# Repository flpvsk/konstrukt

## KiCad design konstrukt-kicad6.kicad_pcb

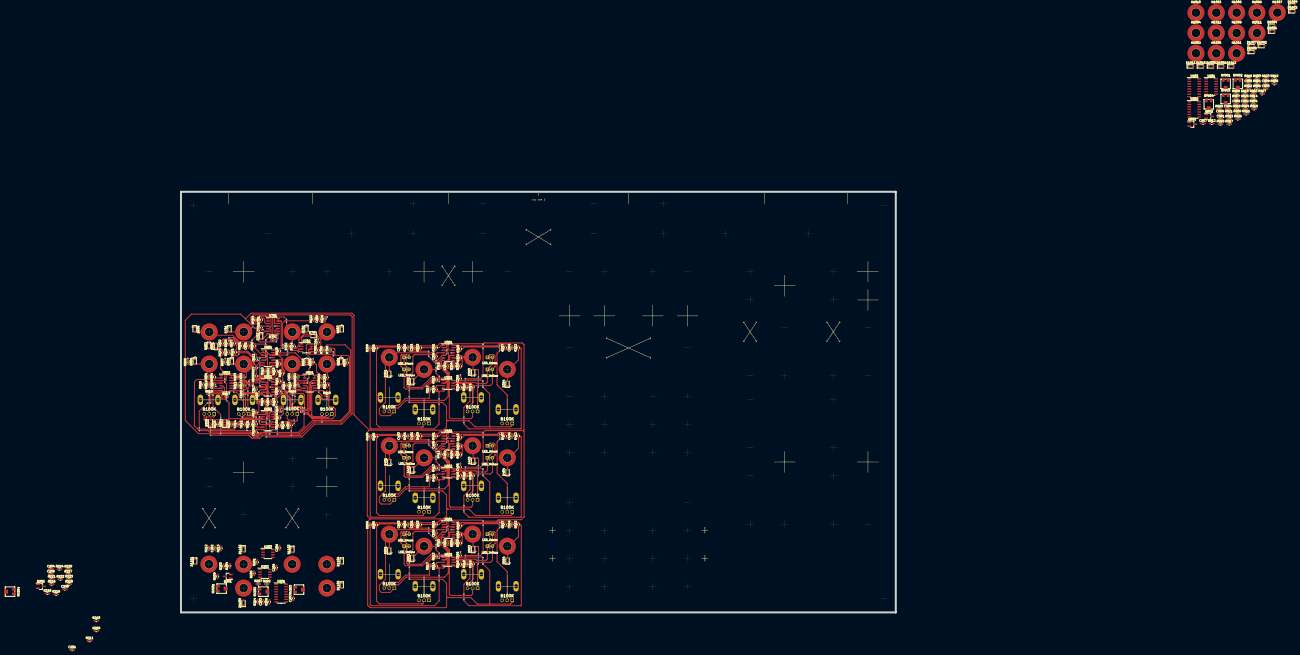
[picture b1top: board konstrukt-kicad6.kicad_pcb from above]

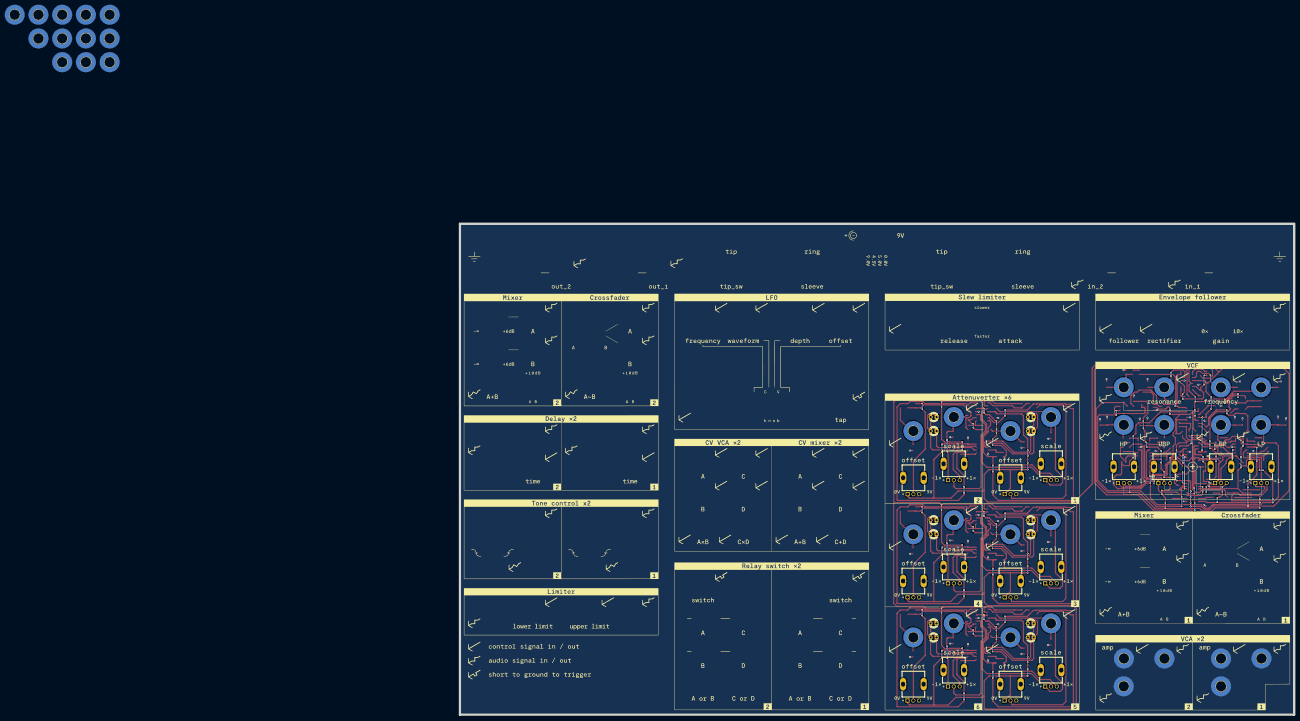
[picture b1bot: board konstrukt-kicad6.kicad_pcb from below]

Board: 2 copper layers, 356.9 x 210.0 mm, 361 parts (54 on the bottom side), 212 nets.

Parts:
C201, C205, C901, C903: 100p; C_0603_1608Metric_Pad1.08x0.95mm_HandSolder
C202, C203, C204, C206, C207, C208, C209, C305, C306, C405, C406, C505, C506, C601, C606, C612, C613, C615, C616, C701, C702, C801, C802, C803, C804, C805, C806, C907, C908, C909: 100n; C_0603_1608Metric_Pad1.08x0.95mm_HandSolder
C301, C302, C303, C304, C401, C402, C403, C404, C501, C502, C503, C504, C902, C904, C905, C906: 10p; C_0603_1608Metric_Pad1.08x0.95mm_HandSolder
C602, C605, C608, C614: 220p; C_0603_1608Metric_Pad1.08x0.95mm_HandSolder
C603, C604, C607, C610: 1.2n; C_0603_1608Metric_Pad1.08x0.95mm_HandSolder
D301, D302, D303, D304, D401, D402, D403, D404, D501, D502, D503, D504, D603, D606, D701, D702, D801, D802, D803, D804, D1001, D1002, D1003, D1004, D1005, D1006, D1007, D1008, D1009, D1010, D1011, D1012, D1101, D1102, D1103, D1104, D1105, D1106: D_TVS; D_SOD-323_HandSoldering
D305, D306, D405, D406, D505, D506: LED_Green; LED_D3.0mm
D307, D308, D407, D408, D507, D508: LED_Yellow; LED_D3.0mm
D601, D602, D703, D704: D; D_SOD-323_HandSoldering
D604, D605: D_Zener; D_SOD-123
H301: 2xAttenuverters1_1_In; MountingHole_4.3mm_M4_Pad_TopBottom
H302: 2xAttenuverters1_1_Out; MountingHole_4.3mm_M4_Pad_TopBottom
H303: 2xAttenuverters1_2_In; MountingHole_4.3mm_M4_Pad_TopBottom
H304: 2xAttenuverters1_2_Out; MountingHole_4.3mm_M4_Pad_TopBottom
H401: 2xAttenuverters2_1_In; MountingHole_4.3mm_M4_Pad_TopBottom
H402: 2xAttenuverters2_1_Out; MountingHole_4.3mm_M4_Pad_TopBottom
H403: 2xAttenuverters2_2_In; MountingHole_4.3mm_M4_Pad_TopBottom
H404: 2xAttenuverters2_2_Out; MountingHole_4.3mm_M4_Pad_TopBottom
H501: 2xAttenuverters3_1_In; MountingHole_4.3mm_M4_Pad_TopBottom
H502: 2xAttenuverters3_1_Out; MountingHole_4.3mm_M4_Pad_TopBottom
H503: 2xAttenuverters3_2_In; MountingHole_4.3mm_M4_Pad_TopBottom
H504: 2xAttenuverters3_2_Out; MountingHole_4.3mm_M4_Pad_TopBottom
H601: Main_Out; MountingHole_4.3mm_M4_Pad_TopBottom
H602: In; MountingHole_4.3mm_M4_Pad_TopBottom
H701: Freq_In; MountingHole_4.3mm_M4_Pad_TopBottom
H702: Res_In; MountingHole_4.3mm_M4_Pad_TopBottom
H801: HP_Out; MountingHole_4.3mm_M4_Pad_TopBottom
H802: UBP_Out; MountingHole_4.3mm_M4_Pad_TopBottom
H803: LBP_Out; MountingHole_4.3mm_M4_Pad_TopBottom
H804: LP_Out; MountingHole_4.3mm_M4_Pad_TopBottom
H1001, H1101: VCA1_In; MountingHole_4.3mm_M4_Pad_TopBottom
H1002, H1102: VCA1_CV_In; MountingHole_4.3mm_M4_Pad_TopBottom
H1003, H1103: VCA2_In; MountingHole_4.3mm_M4_Pad_TopBottom
H1004, H1104: VCA2_CV_In; MountingHole_4.3mm_M4_Pad_TopBottom
H1005, H1105: VCA1_Out; MountingHole_4.3mm_M4_Pad_TopBottom
H1006, H1106: VCA2_Out; MountingHole_4.3mm_M4_Pad_TopBottom
H1007: Mixer1_In1; MountingHole_4.3mm_M4_Pad_TopBottom
H1008: Mixer1_In2; MountingHole_4.3mm_M4_Pad_TopBottom
H1009: Mixer2_In1; MountingHole_4.3mm_M4_Pad_TopBottom
H1010: Mixer2_In2; MountingHole_4.3mm_M4_Pad_TopBottom
H1011: Mixer1_Out; MountingHole_4.3mm_M4_Pad_TopBottom
H1012: Mixer2_Out; MountingHole_4.3mm_M4_Pad_TopBottom
Q201, Q202, Q901, Q902: Q_PNP_BEC; SOT-23_Handsoldering
R201, R206, R210, R222, R627, R905, R917: 30K; R_0603_1608Metric_Pad0.98x0.95mm_HandSolder
R202, R211, R907, R918: 8.2K; R_0603_1608Metric_Pad0.98x0.95mm_HandSolder
R203, R204, R216, R217, R301, R302, R303, R304, R305, R306, R307, R308, R309, R310, R314, R316, R401, R402, R403, R404, R405, R406, R407, R408, R409, R410, R414, R416, R501, R502, R503, R504, R505, R506, R507, R508, R509, R510, R514, R516, R701, R702, R809, R810, R811, R812, R813, R814, R815, R816, R901, R902, R903, R910, R911, R915, R919, R920, R921, R922, R923, R924: 100K; R_0603_1608Metric_Pad0.98x0.95mm_HandSolder
R205, R219, R615, R616, R617, R618, R620, R705, R904, R912: 10K; R_0603_1608Metric_Pad0.98x0.95mm_HandSolder
R207, R220, R311, R312, R411, R412, R511, R512, R622, R703, R704, R707, R708, R801, R802, R803, R804, R906, R913, R914, R925, R926, R928: 1K; R_0603_1608Metric_Pad0.98x0.95mm_HandSolder
R208, R223: 5K; R_0603_1608Metric_Pad0.98x0.95mm_HandSolder
R209, R221, R908, R916: 680; R_0603_1608Metric_Pad0.98x0.95mm_HandSolder
R212, R215, R601: 1M; R_0603_1608Metric_Pad0.98x0.95mm_HandSolder
R213, R214, R218, R224, R606, R628, R805, R806, R807, R808: 200K; R_0603_1608Metric_Pad0.98x0.95mm_HandSolder
R313, R315, R413, R415, R513, R515: 470; R_0603_1608Metric_Pad0.98x0.95mm_HandSolder
R317, R318, R417, R418, R517, R518: 20K; R_0603_1608Metric_Pad0.98x0.95mm_HandSolder
R602, R603, R604, R605, R607, R608, R609, R610, R611, R613, R623, R625, R626, R630: 33K; R_0603_1608Metric_Pad0.98x0.95mm_HandSolder
R612: 22K; R_0603_1608Metric_Pad0.98x0.95mm_HandSolder
R614, R619, R629, R631: 220; R_0603_1608Metric_Pad0.98x0.95mm_HandSolder
R621, R632: 3.3K; R_0603_1608Metric_Pad0.98x0.95mm_HandSolder
R624: 330K; R_0603_1608Metric_Pad0.98x0.95mm_HandSolder
R706: 5.6K; R_0603_1608Metric_Pad0.98x0.95mm_HandSolder
R909, R927: 75K; R_0603_1608Metric_Pad0.98x0.95mm_HandSolder
RV201, RV204, RV901, RV903: 100K; Potentiometer_Bourns_3314J_Vertical
RV202, RV203, RV902, RV904: 1K; Potentiometer_Bourns_3314J_Vertical
RV301, RV302, RV303, RV304, RV401, RV402, RV403, RV404, RV501, RV502, RV503, RV504, RV801, RV802, RV803, RV804: B100K; V2_TRIM_R0904NB10KL-25KQ-
U201, U903: LM13700; SOIC-16_3.9x9.9mm_P1.27mm
U202: MCP6002; SOIC-8_3.9x4.9mm_P1.27mm
U203, U302, U402, U502, U702: TL072; SOIC-8_3.9x4.9mm_P1.27mm
U301, U401, U501, U901, U902: MCP6004; SOIC-14_3.9x8.7mm_P1.27mm
U601, U602, U701, U801, U802: TL074; SOIC-14_3.9x8.7mm_P1.27mm
U603: SSI2164; SOIC-16_3.9x9.9mm_P1.27mm

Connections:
/2xAttenuverters1/2xAudio VCA_1_In: D301.2 (A2), H301.1, R301.1, RV301.1
/2xAttenuverters1/2xAudio VCA_1_Out: D302.2 (A2), H302.1, R311.1
/2xAttenuverters1/2xAudio VCA_2_In: D303.2 (A2), H303.1, R302.1, RV302.1
/2xAttenuverters1/2xAudio VCA_2_Out: D304.2 (A2), H304.1, R312.1
/2xAttenuverters2/2xAudio VCA_1_In: D401.2 (A2), H401.1, R401.1, RV401.1
/2xAttenuverters2/2xAudio VCA_1_Out: D402.2 (A2), H402.1, R411.1
/2xAttenuverters2/2xAudio VCA_2_In: D403.2 (A2), H403.1, R402.1, RV402.1
/2xAttenuverters2/2xAudio VCA_2_Out: D404.2 (A2), H404.1, R412.1
/2xAttenuverters3/2xAudio VCA_1_In: D501.2 (A2), H501.1, R501.1, RV501.1
/2xAttenuverters3/2xAudio VCA_1_Out: D502.2 (A2), H502.1, R511.1
/2xAttenuverters3/2xAudio VCA_2_In: D503.2 (A2), H503.1, R502.1, RV502.1
/2xAttenuverters3/2xAudio VCA_2_Out: D504.2 (A2), H504.1, R512.1
/2xAudio VCA/VCA1_CV: D1102.2 (A2), H1102.1, R204.1
/2xAudio VCA/VCA1_Iabc: R207.1, U201.1
/2xAudio VCA/VCA1_In: C202.1, D1101.2 (A2), H1101.1, R212.1
/2xAudio VCA/VCA1_Out: C203.2, D1105.2 (A2), H1105.1, R214.1
/2xAudio VCA/VCA2_CV: D1104.2 (A2), H1104.1, R217.1
/2xAudio VCA/VCA2_Iabc: R220.1, U201.16
/2xAudio VCA/VCA2_In: C204.1, D1103.2 (A2), H1103.1, R215.1
/2xAudio VCA/VCA2_Out: C208.2, D1106.2 (A2), H1106.1, R224.1
/2xCV VCA & 2xMixer/Mixer1_In1: D1007.2 (A2), H1007.1, R919.1
/2xCV VCA & 2xMixer/Mixer1_In2: D1008.2 (A2), H1008.1, R920.1
/2xCV VCA & 2xMixer/Mixer1_Out: D1011.2 (A2), H1011.1, R925.2
/2xCV VCA & 2xMixer/Mixer2_In1: D1009.2 (A2), H1009.1, R921.1
/2xCV VCA & 2xMixer/Mixer2_In2: D1010.2 (A2), H1010.1, R922.1
/2xCV VCA & 2xMixer/Mixer2_Out: D1012.2 (A2), H1012.1, R926.2
/2xCV VCA & 2xMixer/VCA1_CV_In: D1002.2 (A2), H1002.1, R903.1
/2xCV VCA & 2xMixer/VCA1_Iabc: R906.1, U903.16
/2xCV VCA & 2xMixer/VCA1_In: D1001.2 (A2), H1001.1, R901.2, U901.3 (+)
/2xCV VCA & 2xMixer/VCA1_Out: D1005.2 (A2), H1005.1, R913.2
/2xCV VCA & 2xMixer/VCA2_CV_In: D1004.2 (A2), H1004.1, R911.1
/2xCV VCA & 2xMixer/VCA2_Iabc: R914.1, U903.1
/2xCV VCA & 2xMixer/VCA2_In: D1003.2 (A2), H1003.1, R915.2, U901.10 (+)
/2xCV VCA & 2xMixer/VCA2_Out: D1006.2 (A2), H1006.1, R928.2
/+2V: RV902.2, RV904.2, U901.5 (+), U902.12 (+)
/+4.5V: C603.2, C604.2, C607.2, C610.2, C616.2, D605.1 (K), R206.2, R209.2, R213.1, R218.1, R221.2, R222.2, R313.1, R315.1, R317.2, R318.2, R413.1, R415.1, R417.2, R418.2, R513.1, R515.1, R517.2, R518.2, R604.1, R606.2, R608.1, R701.2, R702.2, R706.1, R901.1, R908.2, R915.1, R916.2, RV202.2, RV203.2, RV301.3, RV302.3, RV401.3, RV402.3, RV501.3, RV502.3, RV801.3, RV802.3, RV803.3, RV804.3, U202.3 (+), U202.5 (+), U301.5 (+), U301.12 (+), U401.5 (+), U401.12 (+), U501.5 (+), U501.12 (+), U601.5 (+), U601.12 (+), U602.3 (+), U602.5 (+), U602.10 (+), U602.12 (+), U603.8 (GND), U701.5 (+), U702.3 (+), U901.12 (+), U902.3 (+), U902.5 (+), U902.10 (+)
/+9V: C206.1, C207.1, C209.1, C305.1, C306.1, C405.1, C406.1, C505.1, C506.1, C612.2, C613.2, C615.1, C701.2, C702.2, C805.2, C806.2, C907.1, C908.1, C909.1, R202.1, R211.1, R907.1, R918.1, RV201.1, RV204.1, RV303.1, RV304.1, RV403.1, RV404.1, RV503.1, RV504.1, RV901.1, RV903.1, U201.11 (V+), U202.8 (V+), U203.8 (V+), U301.4 (V+), U302.8 (V+), U401.4 (V+), U402.8 (V+), U501.4 (V+), U502.8 (V+), U601.4 (V+), U602.4 (V+), U603.16 (V+), U701.4 (V+), U702.8 (V+), U801.4 (V+), U802.4 (V+), U901.4 (V+), U902.4 (V+), U903.11 (V+)
/GND: C206.2, C207.2, C209.2, C305.2, C306.2, C405.2, C406.2, C505.2, C506.2, C612.1, C613.1, C615.2, C616.1, C701.1, C702.1, C805.1, C806.1, C907.2, C908.2, C909.2, D301.1 (A1), D302.1 (A1), D303.1 (A1), D304.1 (A1), D401.1 (A1), D402.1 (A1), D403.1 (A1), D404.1 (A1), D501.1 (A1), D502.1 (A1), D503.1 (A1), D504.1 (A1), D603.1 (A1), D606.1 (A1), D701.1 (A1), D702.1 (A1), D801.1 (A1), D802.1 (A1), D803.1 (A1), D804.1 (A1), D1001.1 (A1), D1002.1 (A1), D1003.1 (A1), D1004.1 (A1), D1005.1 (A1), D1006.1 (A1), D1007.1 (A1), D1008.1 (A1), D1009.1 (A1), D1010.1 (A1), D1011.1 (A1), D1012.1 (A1), D1101.1 (A1), D1102.1 (A1), D1103.1 (A1), D1104.1 (A1), D1105.1 (A1), D1106.1 (A1), R208.2, R212.2, R214.2, R215.2, R223.2, R224.2, R601.2, R628.2, R805.2, R806.2, R807.2, R808.2, RV201.3, RV204.3, RV301.0 (ShieldPin), RV302.0 (ShieldPin), RV303.0 (ShieldPin), RV303.3, RV304.0 (ShieldPin), RV304.3, RV401.0 (ShieldPin), RV402.0 (ShieldPin), RV403.0 (ShieldPin), RV403.3, RV404.0 (ShieldPin), RV404.3, RV501.0 (ShieldPin), RV502.0 (ShieldPin), RV503.0 (ShieldPin), RV503.3, RV504.0 (ShieldPin), RV504.3, RV801.0 (ShieldPin), RV802.0 (ShieldPin), RV803.0 (ShieldPin), RV804.0 (ShieldPin), RV901.3, RV903.3, U201.6 (V-), U202.4 (V-), U203.4 (V-), U301.11 (V-), U302.4 (V-), U401.11 (V-), U402.4 (V-), U501.11 (V-), U502.4 (V-), U601.11 (V-), U602.11 (V-), U603.9 (V-), U701.11 (V-), U702.4 (V-), U801.11 (V-), U802.11 (V-), U901.11 (V-), U902.11 (V-), U903.6 (V-), U903.7, U903.10
/VCF/(UBP-LBP)/2_Clip: D601.1 (K), D602.2 (A), R624.2
/VCF/FB: R609.1, R627.2, U601.7
/VCF/HP: R611.2, R613.1, R809.1, RV801.1, U602.14, U801.12 (+)
/VCF/HP_Vert: R615.1, R813.2, U801.8
/VCF/In: C601.1, D606.2 (A2), H602.1, R601.1
/VCF/LBP: C608.2, R602.1, R630.1, R811.1, RV803.1, U602.7, U802.12 (+)
/VCF/LBP_Vert: R617.1, R815.2, U802.8
/VCF/LP: C614.2, R632.1, R812.1, RV804.1, U602.1, U802.3 (+)
/VCF/LP_Clip: D604.1 (K), R625.1, R632.2
/VCF/LP_Vert: R618.1, R816.2, U802.7
/VCF/Out: C606.2, D603.2 (A2), H601.1, R628.1
/VCF/UBP: C605.2, R603.1, R626.1, R810.1, RV802.1, U602.8, U801.3 (+)
/VCF/UBP-LBP: C602.2, R605.2, R607.2, R612.1, R621.1, U601.8
/VCF/UBP_Vert: R616.1, R814.2, U801.7
/VCF/VCA_I_In1: R612.2, R614.1, U603.2 (I_IN1)
/VCF/VCA_I_In2: R630.2, R631.1, U603.7 (I_IN2)
/VCF/VCA_I_In3: R626.2, R629.1, U603.10 (I_IN3)
/VCF/VCA_I_In4: R613.2, R619.1, U603.15 (I_IN4)
/VCF/VCA_I_Out1: R623.2, R624.1, R625.2, R627.1, U601.6 (-), U603.4 (I_OUT1)
/VCF/VCA_I_Out2: C614.1, U602.2 (-), U603.5 (I_OUT2)
/VCF/VCA_I_Out3: C608.1, U602.6 (-), U603.12 (I_OUT3)
/VCF/VCA_I_Out4: C605.1, U602.9 (-), U603.13 (I_OUT4)
/VCF/VCA_VC1: R707.2, U603.3 (VC1), U603.6 (VC2), U603.11 (VC3)
/VCF/VCA_VC4: R708.2, U603.14 (VC4)
/VCF/VCF Audio Outs/HP_Out: C801.2, D801.2 (A2), H801.1, R805.1
/VCF/VCF Audio Outs/LBP_Out: C803.2, D803.2 (A2), H803.1, R807.1
/VCF/VCF Audio Outs/LP_Out: C804.2, D804.2 (A2), H804.1, R808.1
/VCF/VCF Audio Outs/UBP_Out: C802.2, D802.2 (A2), H802.1, R806.1
/VCF/VCF CV Ins/Freq_In: D701.2 (A2), H701.1, R701.1, U701.3 (+)
/VCF/VCF CV Ins/Res_In: D702.2 (A2), H702.1, R702.1, U701.12 (+)
unnamed: C201.1, R203.2, R204.2, R205.1, U202.2 (-)
unnamed: C201.2, Q201.2 (E), R205.2, R209.1
unnamed: C202.2, R213.2, U203.3 (+)
unnamed: C204.2, R218.2, U203.5 (+)
unnamed: C205.1, R216.2, R217.2, R219.1, U202.6 (-)
unnamed: C205.2, Q202.2 (E), R219.2, R221.1
unnamed: C208.1, R223.1, U201.9
unnamed: C301.1, R301.2, R303.2, U301.2 (-)
unnamed: C301.2, R303.1, R306.2, U301.1
unnamed: C302.1, R302.2, R304.2, U301.9 (-)
unnamed: C302.2, R304.1, R308.2, U301.8
unnamed: C303.1, R305.1, R306.1, R309.2, U301.6 (-)
unnamed: C303.2, R309.1, R311.2, R314.2, U301.7
unnamed: C304.1, R307.1, R308.1, R310.2, U301.13 (-)
unnamed: C304.2, R310.1, R312.2, R316.2, U301.14
unnamed: C401.1, R401.2, R403.2, U401.2 (-)
unnamed: C401.2, R403.1, R406.2, U401.1
unnamed: C402.1, R402.2, R404.2, U401.9 (-)
unnamed: C402.2, R404.1, R408.2, U401.8
unnamed: C403.1, R405.1, R406.1, R409.2, U401.6 (-)
unnamed: C403.2, R409.1, R411.2, R414.2, U401.7
unnamed: C404.1, R407.1, R408.1, R410.2, U401.13 (-)
unnamed: C404.2, R410.1, R412.2, R416.2, U401.14
unnamed: C501.1, R501.2, R503.2, U501.2 (-)
unnamed: C501.2, R503.1, R506.2, U501.1
unnamed: C502.1, R502.2, R504.2, U501.9 (-)
unnamed: C502.2, R504.1, R508.2, U501.8
unnamed: C503.1, R505.1, R506.1, R509.2, U501.6 (-)
unnamed: C503.2, R509.1, R511.2, R514.2, U501.7
unnamed: C504.1, R507.1, R508.1, R510.2, U501.13 (-)
unnamed: C504.2, R510.1, R512.2, R516.2, U501.14
unnamed: C601.2, R606.1, U601.3 (+)
unnamed: C602.1, D601.2 (A), D602.1 (K), R607.1, R608.2
unnamed: C603.1, R614.2
unnamed: C604.1, R619.2
unnamed: C606.1, R622.2
unnamed: C607.1, R629.2
unnamed: C610.1, R631.2
unnamed: C801.1, R801.2
unnamed: C802.1, R802.2
unnamed: C803.1, R803.2
unnamed: C804.1, R804.2
unnamed: C901.1, R902.2, R903.2, R904.1, U902.2 (-)
unnamed: C901.2, Q901.2 (E), R904.2, R908.1
unnamed: C902.1, R909.2, R913.1, U901.7
unnamed: C902.2, R909.1, U901.6 (-), U903.12
unnamed: C903.1, R910.2, R911.2, R912.1, U902.6 (-)
unnamed: C903.2, Q902.2 (E), R912.2, R916.1
unnamed: C904.1, R919.2, R920.2, R923.1, U902.9 (-)
unnamed: C904.2, R923.2, R925.1, U902.8
unnamed: C905.1, R921.2, R922.2, R924.1, U901.13 (-)
unnamed: C905.2, R924.2, R926.1, U901.14
unnamed: C906.1, R927.2, R928.1, U902.14
unnamed: C906.2, R927.1, U902.13 (-), U903.5
unnamed: D305.1 (K), D307.2 (A), R313.2, U302.2 (-)
unnamed: D305.2 (A), D307.1 (K), U302.1
unnamed: D306.1 (K), D308.2 (A), R315.2, U302.6 (-)
unnamed: D306.2 (A), D308.1 (K), U302.7
unnamed: D405.1 (K), D407.2 (A), R413.2, U402.2 (-)
unnamed: D405.2 (A), D407.1 (K), U402.1
unnamed: D406.1 (K), D408.2 (A), R415.2, U402.6 (-)
unnamed: D406.2 (A), D408.1 (K), U402.7
unnamed: D505.1 (K), D507.2 (A), R513.2, U502.2 (-)
unnamed: D505.2 (A), D507.1 (K), U502.1
unnamed: D506.1 (K), D508.2 (A), R515.2, U502.6 (-)
unnamed: D506.2 (A), D508.1 (K), U502.7
unnamed: D604.2 (A), D605.2 (A)
unnamed: D703.1 (K), R703.2, U701.6 (-), U701.10 (+)
unnamed: D703.2 (A), U701.7
unnamed: D704.1 (K), R704.2, R705.1, U702.2 (-)
unnamed: D704.2 (A), U702.1
unnamed: Q201.1 (B), U202.1
unnamed: Q201.3 (C), R207.2
unnamed: Q202.1 (B), U202.7
unnamed: Q202.3 (C), R220.2
unnamed: Q901.1 (B), U902.1
unnamed: Q901.3 (C), R906.2
unnamed: Q902.1 (B), U902.7
unnamed: Q902.3 (C), R914.2
unnamed: R201.1, U203.1, U203.2 (-)
unnamed: R201.2, RV202.1, U201.3 (+)
unnamed: R202.2, U201.2 (DIODE_BIAS)
unnamed: R203.1, RV201.2
unnamed: R206.1, U201.5, U201.7
unnamed: C203.1, R208.1, U201.8
unnamed: R210.1, U203.6 (-), U203.7
unnamed: R210.2, RV203.1, U201.14 (+)
unnamed: R211.2, U201.15 (DIODE_BIAS)
unnamed: R216.1, RV204.2
unnamed: R222.1, U201.10, U201.12
unnamed: R305.2, RV303.2
unnamed: R307.2, RV304.2
unnamed: R314.1, R317.1, U302.3 (+)
unnamed: R316.1, R318.1, U302.5 (+)
unnamed: R405.2, RV403.2
unnamed: R407.2, RV404.2
unnamed: R414.1, R417.1, U402.3 (+)
unnamed: R416.1, R418.1, U402.5 (+)
unnamed: R505.2, RV503.2
unnamed: R507.2, RV504.2
unnamed: R514.1, R517.1, U502.3 (+)
unnamed: R516.1, R518.1, U502.5 (+)
unnamed: R602.2, R605.1, U601.9 (-)
unnamed: R603.2, R604.2, U601.10 (+)
unnamed: R609.2, R610.2, R611.1, U602.13 (-)
unnamed: R610.1, U601.1, U601.2 (-)
unnamed: R615.2, R616.2, R617.2, R618.2, R620.1, U601.13 (-)
unnamed: R620.2, R622.1, U601.14
unnamed: R621.2, R623.1
unnamed: R703.1, U701.1, U701.2 (-)
unnamed: R704.1, U701.13 (-), U701.14
unnamed: R705.2, R706.2, U702.5 (+)
unnamed: R707.1, U701.8, U701.9 (-)
unnamed: R708.1, U702.6 (-), U702.7
unnamed: R801.1, U801.13 (-), U801.14
unnamed: R802.1, U801.1, U801.2 (-)
unnamed: R803.1, U802.13 (-), U802.14
unnamed: R804.1, U802.1, U802.2 (-)
unnamed: R809.2, R813.1, U801.9 (-)
unnamed: R810.2, R814.1, U801.6 (-)
unnamed: R811.2, R815.1, U802.9 (-)
unnamed: R812.2, R816.1, U802.6 (-)
unnamed: R902.1, RV901.2
unnamed: R905.1, U901.1, U901.2 (-)
unnamed: R905.2, RV902.1, U903.14 (+)
unnamed: R907.2, U903.15 (DIODE_BIAS)
unnamed: R910.1, RV903.2
unnamed: R917.1, U901.8, U901.9 (-)
unnamed: R917.2, RV904.1, U903.3 (+)
unnamed: R918.2, U903.2 (DIODE_BIAS)
unnamed: RV202.3, U201.4 (-)
unnamed: RV203.3, U201.13 (-)
unnamed: RV301.2, U301.3 (+)
unnamed: RV302.2, U301.10 (+)
unnamed: RV401.2, U401.3 (+)
unnamed: RV402.2, U401.10 (+)
unnamed: RV501.2, U501.3 (+)
unnamed: RV502.2, U501.10 (+)
unnamed: RV801.2, U801.10 (+)
unnamed: RV802.2, U801.5 (+)
unnamed: RV803.2, U802.10 (+)
unnamed: RV804.2, U802.5 (+)
unnamed: RV902.3, U903.13 (-)
unnamed: RV904.3, U903.4 (-)

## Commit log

2023-05-05 Init
2023-05-06 Fix: Raise LED driver input impedance
2023-05-12 PT2399 voltage control
2023-05-13 Add switch circuits
2023-05-13 Transistor invertor didnt work, try opamp
2023-05-17 Switch verified
2023-05-17 CV limiter for VCF
2023-05-24 Started schem capture
2023-05-24 Add circuitjs for verified blocks
2023-05-26 Attenuverter board wip
2023-05-27 Attenuverters laid out
2023-05-27 Add rectified out to env follower circuitjs
2023-05-27 Design CV VCA, CV Mixer, Env Follower
2023-05-31 Add unverified lfo cv bias circuit
2023-05-31 LFO bias circuit not great
2023-05-31 LFO design
2023-06-01 Relay switch design
2023-06-01 Fix attenuverter pots + more design
2023-06-02 more design tetris
2023-06-03 All modules in place in affinity
2023-06-07 Getting ready for design export
2023-06-07 Moved design to the PCB
2023-06-07 Add exported design svg
2023-06-08 VCF schem capture
2023-06-09 VCF schem combed
2023-06-09 Start VCF layout
2023-06-10 WIP VCF Layout
2023-06-14 VCF layout wip
2023-06-14 VCF layout done, vca capture
2023-06-14 vcas layout wip
2023-06-15 CV VCA layout
2023-06-15 CV VCA / Mixer wip
2023-06-15 CV VCA Mixer & audio VCA layout done
2023-06-15 LFO design and bias circuit
2023-06-15 Design tetris
2023-06-15 VCF layout
2023-06-15 CV VCA & Mixer, Audio VCA schem capture
2023-06-15 CV VCA & Mixer, Audio Mixer layout
2023-06-15 Envelope Follower schem capture
2023-06-16 Envelope follower layout done
2023-06-19 Delay schem capture done
2023-06-20 Delay layout done
2023-06-20 Mixer/Crossfader schem capture done
2023-06-21 Mixer/Crossfader layout done
2023-06-23 LFO schem init
2023-06-23 LFO layout down
2023-06-23 LFO schem capture done / replace r2r opamps
2023-06-23 Add envelope follower gain stage
2023-06-26 Relay switch schem capture done
2023-06-26 Relay switch layout done
2023-06-27 Tone control schematic & layout
2023-06-27 VC-limiter schem & layout
2023-06-27 Update attenuverter labels to get rid of warnings
2023-06-28 Slew limiter schem capture done
2023-06-28 Slew limiter layout done
2023-06-28 Increase the size of dc blocking caps
2023-06-28 PSU schem capture done
2023-06-29 PSU schem update
2023-06-29 Jacks schem done
2023-07-01 Mixer redesign wip
2023-07-01 Power & jacks layout done
2023-07-01 Updated silk screen for jacks
2023-07-01 Swap ins horizontaly on mixer
2023-07-01 Add mounting holes
2023-07-01 Small pcb fixes
2023-07-01 Fix: crossfader pot orientation
2023-07-01 Switch VCF cv processing opamps
2023-07-01 Add JLC parts numbers
2023-07-01 Added JLC order number
2023-07-01 Update version graphic
2023-07-01 JLC Order
2023-07-01 Clear TODOs
2023-08-03 new vcf cv bias verified
2023-08-30 lfo cv processing
2023-10-20 ringmod
2023-10-26 varislope osc
